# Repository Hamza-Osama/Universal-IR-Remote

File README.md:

# Universal-IR-Remote
Arduino based remote with receiver and transmitter, where you can copy IR code from any remote, assign to a button, and transmit on command.

## Design
### Schematic

### PCB

### 3D Visualization

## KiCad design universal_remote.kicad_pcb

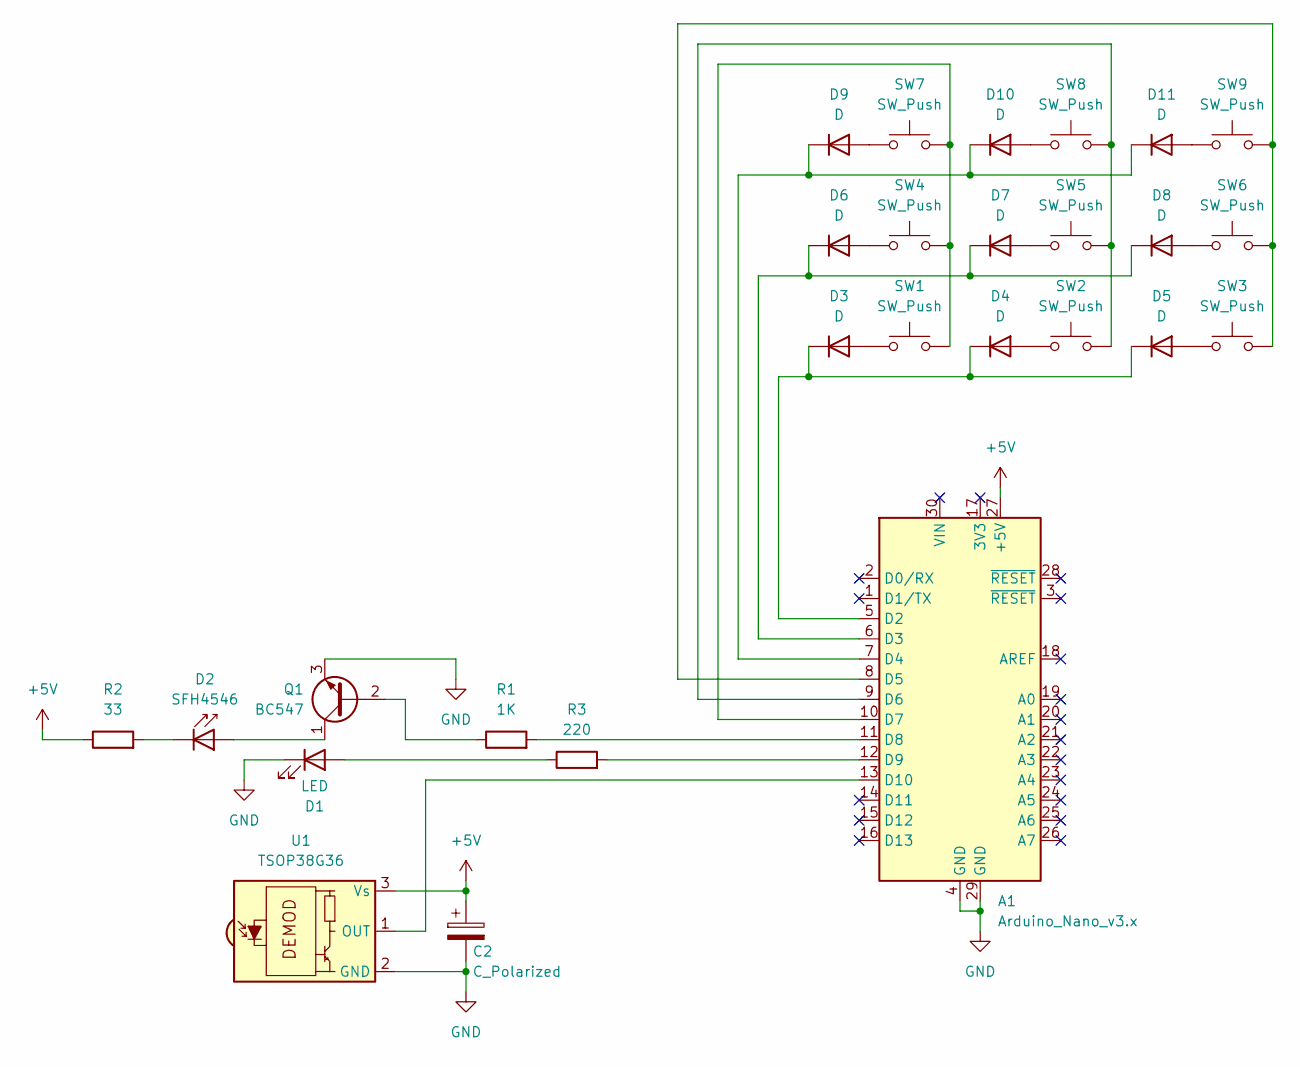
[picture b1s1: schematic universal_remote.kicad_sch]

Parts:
A1: Arduino_Nano_v3.x; Arduino_Nano
C2: C_Polarized; CP_Radial_D5.0mm_P2.00mm
D1: LED; LED_D5.0mm
D2: SFH4546; LED_D5.0mm_IRGrey
D3, D4, D5, D6, D7, D8, D9, D10, D11: D; D_DO-35_SOD27_P7.62mm_Horizontal
Q1: BC547; TO-92_Inline
R1: 1K; R_Axial_DIN0207_L6.3mm_D2.5mm_P7.62mm_Horizontal
R2: 33; R_Axial_DIN0207_L6.3mm_D2.5mm_P7.62mm_Horizontal
R3: 220; R_Axial_DIN0207_L6.3mm_D2.5mm_P7.62mm_Horizontal
SW1, SW2, SW3, SW4, SW5, SW6, SW7, SW8, SW9: SW_Push; SW_PUSH_6mm
U1: TSOP38G36; Vishay_MINICAST-3Pin

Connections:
+5V: A1.27 (+5V), C2.1, R2.1, U1.3 (Vs)
GND: A1.4 (GND), A1.29 (GND), C2.2, D1.1 (K), Q1.3 (E), U1.2 (GND)
unnamed: A1.5 (D2), D3.1 (K), D4.1 (K), D5.1 (K)
unnamed: A1.6 (D3), D6.1 (K), D7.1 (K), D8.1 (K)
unnamed: A1.7 (D4), D9.1 (K), D10.1 (K), D11.1 (K)
unnamed: A1.8 (D5), SW3.2, SW6.2, SW9.2
unnamed: A1.9 (D6), SW2.2, SW5.2, SW8.2
unnamed: A1.10 (D7), SW1.2, SW4.2, SW7.2
unnamed: A1.11 (D8), R1.2
unnamed: A1.12 (D9), R3.2
unnamed: A1.13 (D10), U1.1 (OUT)
unnamed: D1.2 (A), R3.1
unnamed: D2.2 (A), Q1.1 (C)
unnamed: D2.1 (K), R2.2
unnamed: D3.2 (A), SW1.1
unnamed: D4.2 (A), SW2.1
unnamed: D5.2 (A), SW3.1
unnamed: D6.2 (A), SW4.1
unnamed: D7.2 (A), SW5.1
unnamed: D8.2 (A), SW6.1
unnamed: D9.2 (A), SW7.1
unnamed: D10.2 (A), SW8.1
unnamed: D11.2 (A), SW9.1
unnamed: Q1.2 (B), R1.1

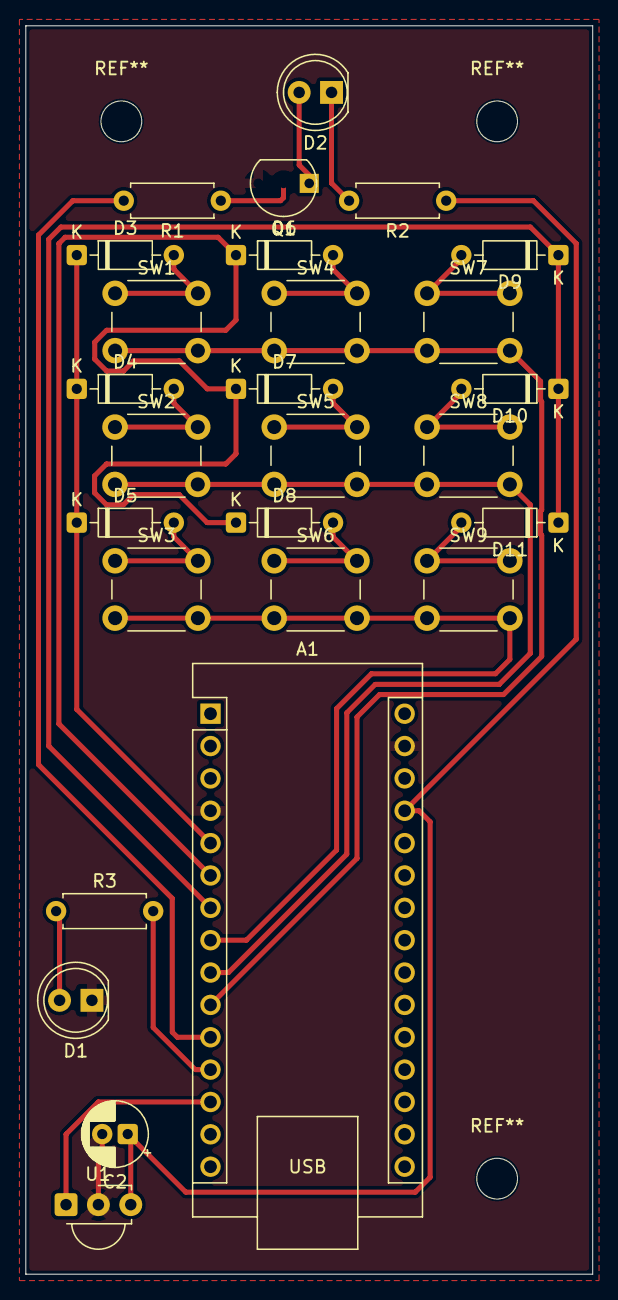
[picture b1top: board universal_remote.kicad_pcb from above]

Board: 2 copper layers, 44.5 x 98.0 mm, 27 parts (0 on the bottom side), 24 nets.

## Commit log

2026-04-01 V1.5 Design + Gerbers
2026-04-02 Adjusted min annular width
2026-04-02 Organizing files
2026-06-08 Adding pictures
